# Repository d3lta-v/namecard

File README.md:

# Ziyue's Namecard

> An enhanced µCurrent Gold and tinyCurrent Derivative

Hi, Ziyue here! You probably received my namecard and you might be wondering what it is or how to use it. It is a fully functional professional low current measurement device, derived from the [µCurrent](https://www.eevblog.com/projects/ucurrent/) made by Dave Jones of EEVBLOG fame, and [tinyCurrent](https://github.com/nfhw/tinycurrent) by [n-fuse GmbH](https://www.n-fuse.co/contact.html). Handy for an EE engineer and a great addition to any EE lab. 

This version has several enhancements that makes it even better for measuring modern devices, especially if you work extensively with USB powered and embedded MCU / RF devices with fast current transients:

- **BNC Connector** to reduce pickup noise while measuring with an oscilloscope. You can use a short BNC female-female adapter to plug this device directly into your oscilloscope instead of relying on a banana jack to BNC cable
- **Higher Positive Dynamic Current Range** by soldering the JP1 jumper closed, up to 2.5A. This will disable sensing of negative currents, which will be clipped to 0V on the voltage output
- **Dedicated USB-C Ports** for current profiling a USB device directly, such as a microcontroller, RF module or other power constrained IoT devices
- **SMD Pads for optional C5, C6 capacitors** to add capacitors on virtual ground rails which prevents oscillation with capacitive loads

## Kit Contents

- PCB with all SMD components pre-soldered
- 2x DP3T switches
- 4x Banana jacks, 2 red and 2 black
- 1x CR2032 battery holder
- 1x BNC connector

Batteries not included, you will need to use your own CR2032 battery

Please solder the through hole components onto the board as per the instructions below.

> [!WARNING]
> The first revision of this board has a silkscreen defect. The battery holder must be soldered in the OPPOSITE direction as indicated by the silkscreen. Refer to the image in the steps below for the correct orientation

1. Solder the CR2032 battery holder
    - 
    - Alternatively, you can also solder wires directly to the battery terminals to attach an external power supply. Ensure your choice of external power is extremely linear with very low noise. Primary cells such as batteries are most suitable for this
2. Solder the BNC connector
    - 
3. Solder the two DP3T slide switches
    - 
4. Screw in the 4 banana jacks into all of the terminals, ensuring that the colors are matched to the positive/negative terminals
    - 
5. (Optional) Solder the JP1 jumper if you do not intend to measure any negative currents. Doing this will double the dynamic range of the device.

## Usage

1. Connect the device under test in loop **on the low side** so that the current flow is from **+** to **-**.
2. Connect a suitable voltage measurement device such as a digital multimeter or an oscilloscope (via BNC) on the output side via either the banana jacks or BNC connector.
3. Turn on the device and read the current on the voltage measurement device in the mV range as if it were mA/µA/nA.

A demo of using this device with an oscilloscope can be seen below:

https://github.com/user-attachments/assets/78531d4b-4d0c-471a-add1-b3f7db313485

## Specifications

### Absolute Maximum Ratings

| Parameter                        | Test Conditions | Min | Typ | Max | Unit |
| -------------------------------- | --------------- | --- | --- | --- | ---- |
| $I_{\text{max}}$ Maximum current |                 |     |     | 5   | A    |
| $V_{\text{cc}}$ Supply voltage   |                 |     |     | 5.5 | V    |

> [!WARNING]
> This device has NO input current protection to reduce burden voltage to a minimum. Do NOT overload the device.

### Electrical Characteristics

| Parameter                                             | Test Conditions             | Min   | Typ  | Max  | Unit   |
| ----------------------------------------------------- | --------------------------- | ----- | ---- | ---- | ------ |
| $I_{\text{nA}}$ Dynamic range of current in nA mode   | $V_{\text{cc}}=2.9\text{V}$ | -1250 |      | 1250 | nA     |
| $I_{\mu\text{A}}$ Dynamic range of current in µA mode | $V_{\text{cc}}=2.9\text{V}$ | -1250 |      | 1250 | µA     |
| $I_{\text{mA}}$ Dynamic range of current in mA mode   | $V_{\text{cc}}=2.9\text{V}$ | -1250 |      | 1250 | mA     |
| $V_{\text{cc}}$ Supply voltage                        |                             | 2.65  |      | 4.5    | V      |
| Resolution in nA mode                                 | On 3.5 digit DMM            |       | 1000 |      | pA     |
|                                                       | On 4.5 digit DMM            |       | 100  |      | pA     |
|                                                       | On 5.5 digit DMM            |       | 10   |      | pA     |
| Accuracy                                              | In µA and nA ranges         | -0.05 |      | 0.05 | %      |
|                                                       | In mA range                 | -0.1  |      | 0.1  | %      |
| $V_{\text{o,off}}$ Output Offset Voltage              |                             | -30   |      | 30   | µV     |
| Temperature Drift                                     | In µA and nA ranges         |       |      | 10   | ppm/˚C |
|                                                       | In mA range                 |       |      | 15   | ppm/˚C |
| Noise                                                 |                             |       |      | -90  | dBV    |
| THD                                                   |                             |       |      | -60  | dB     |
| Bandwidth (-3dB)                                      |                             |       | 300  |      | kHz    |

> Note that in nA mode, contact resistance will need to be accounted for, with an additional 10 µV bias on the output voltage due to the shunt resistor.

In ordinary operations in which virtual ground voltage $V_{\text{VGND}}=\frac{V_{\text{cc}}}{2}$, you can calculate the output voltage dynamic range using the formula:

$$
V_{\text{dynamic}} = \pm \left(\frac{V_{\text{cc}}}{2} - 200 \text{mV}\right)
$$

If you short the JP1 jumper, which sets the virtual ground voltage $V_{\text{VGND}}=0$, the new dynamic range will purely be in the positive range:

$$
V_{\text{dynamic}} = V_{\text{cc}} - 200 \text{mV}
$$

In general, this board has similar specifications to the [original µCurrent Gold](https://www.eevblog.com/projects/ucurrent/).

## Licenses

The circuit schematics of this project are made available under the
[CC-BY-SA](https://creativecommons.org/licenses/by-sa/3.0/) license.

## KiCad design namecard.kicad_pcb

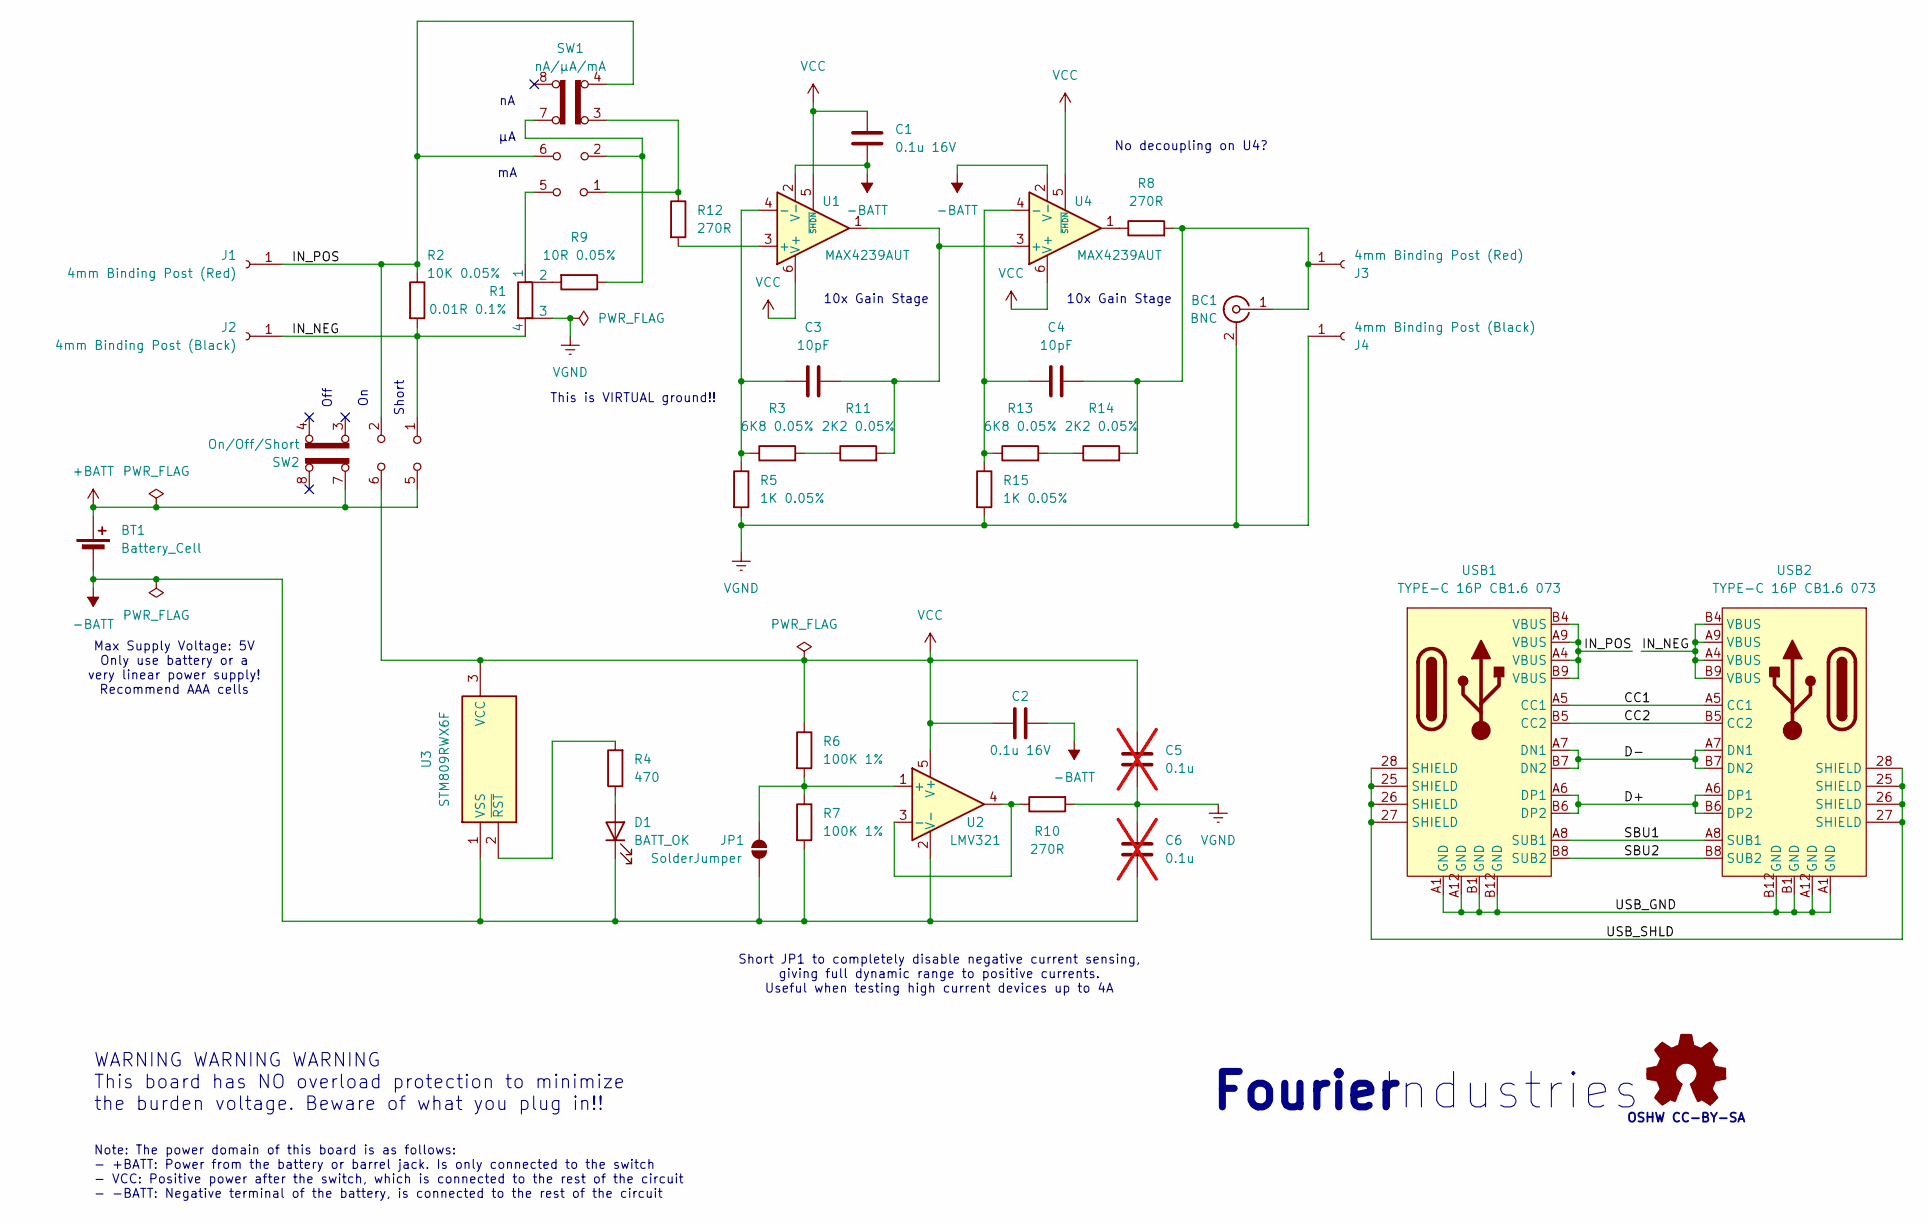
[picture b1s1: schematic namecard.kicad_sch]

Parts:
BC1: BNC; 0731000105
BT1: Battery_Cell; Battery_BAT-TH_BS-02-A1AJ010; JLCPCB C5239862
C1, C2: 0.1u 16V; C_0603_1608Metric
C3, C4: 10pF; C_0603_1608Metric
C5, C6: 0.1u; C_0805_2012Metric; not fitted
D1: BATT_OK; LED_0805_2012Metric; JLCPCB C2296
J1, J3: 4mm Binding Post (Red); Banana_Jack_1Pin_4mm
J2, J4: 4mm Binding Post (Black); Banana_Jack_1Pin_4mm
JP1: SolderJumper; SolderJumper-2_P1.3mm_Open_TrianglePad1.0x1.5mm
R1: 0.01R 0.1%; R_Shunt_Resi_PCSR2512_6332Metric
R2: 10K 0.05%; R_0603_1608Metric
R3, R13: 6K8 0.05%; R_0603_1608Metric
R4: 470; R_0603_1608Metric
R5, R15: 1K 0.05%; R_0603_1608Metric
R6, R7: 100K 1%; R_0603_1608Metric
R8, R10, R12: 270R; R_0603_1608Metric
R9: 10R 0.05%; R_0805_2012Metric
R11, R14: 2K2 0.05%; R_0603_1608Metric
SW1: nA/µA/mA; L203111MS02Q
SW2: On/Off/Short; L203111MS02Q
SYM1: Logo_Open_Hardware_Small; OSHW-Logo2_9.8x8mm_SilkScreen
U1, U4: MAX4239AUT; SOT-23-6
U2: LMV321; SOT-23-5; JLCPCB C7972
U3: STM809RWX6F; SOT103P237X112-3N; Manufacturer_Part_Number STM809RWX6F; Mouser Part Number 511-STM809RWX6F
USB1, USB2: TYPE-C 16P CB1.6 073; USB-C-SMD_SHOU_TYPE-C-16P-CB1.6; LCSC Part C2906290

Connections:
+BATT: BT1.1 (+), SW2.5 (B), SW2.7 (C)
-BATT: BT1.2 (-), C1.2, C2.2, C6.2, D1.1 (K), JP1.1 (A), R7.2, U1.2 (V-), U2.2 (V-), U3.1 (VSS), U4.2 (V-)
/CC1: USB1.A5 (CC1), USB2.A5 (CC1)
/CC2: USB1.B5 (CC2), USB2.B5 (CC2)
/D+: USB1.A6 (DP1), USB1.B6 (DP2), USB2.A6 (DP1), USB2.B6 (DP2)
/D-: USB1.A7 (DN1), USB1.B7 (DN2), USB2.A7 (DN1), USB2.B7 (DN2)
/IN_NEG: J2.1, R1.4, R2.2, SW2.1 (A), USB2.A4 (VBUS), USB2.A9 (VBUS), USB2.B4 (VBUS), USB2.B9 (VBUS)
/IN_POS: J1.1, R2.1, SW1.4 (A), SW1.6 (C), SW2.2 (B), USB1.A4 (VBUS), USB1.A9 (VBUS), USB1.B4 (VBUS), USB1.B9 (VBUS)
/SBU1: USB1.A8 (SUB1), USB2.A8 (SUB1)
/SBU2: USB1.B8 (SUB2), USB2.B8 (SUB2)
/USB_GND: USB1.A1 (GND), USB1.A12 (GND), USB1.B1 (GND), USB1.B12 (GND), USB2.A1 (GND), USB2.A12 (GND), USB2.B1 (GND), USB2.B12 (GND)
/USB_SHLD: USB1.25 (SHIELD), USB1.26 (SHIELD), USB1.27 (SHIELD), USB1.28 (SHIELD), USB2.25 (SHIELD), USB2.26 (SHIELD), USB2.27 (SHIELD), USB2.28 (SHIELD)
unnamed: BC1.1 (In), C4.2, J3.1, R8.2, R14.2
unnamed: D1.2 (A), R4.1
unnamed: JP1.2 (B), R6.2, R7.1, U2.1 (+)
unnamed: R1.1, SW1.5 (B)
unnamed: R1.2, R9.2
unnamed: R8.1, U4.1
unnamed: R9.1, SW1.2 (B), SW1.7 (C)
unnamed: R3.2, R11.1
unnamed: R12.1, SW1.1 (A), SW1.3 (C)
unnamed: R13.2, R14.1
unnamed: R12.2, U1.3 (+)
unnamed: C3.1, R3.1, R5.1, U1.4 (-)
unnamed: R10.1, U2.3 (-), U2.4
unnamed: R4.2, U3.2 (~RST)
unnamed: C3.2, R11.2, U1.1, U4.3 (+)
unnamed: C4.1, R13.1, R15.1, U4.4 (-)
VCC: C1.1, C2.1, C5.1, R6.1, SW2.6 (C), U1.5 (~SHDN), U1.6 (V+), U2.5 (V+), U3.3 (VCC), U4.5 (~SHDN), U4.6 (V+)
VGND: BC1.2 (Ext), C5.2, C6.1, J4.1, R1.3, R5.2, R10.2, R15.2

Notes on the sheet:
Fourier
Industries
10x Gain Stage
Off
This is VIRTUAL ground!!
WARNING WARNING WARNING This board has NO overload protection to minimize the burden voltage. Beware of what you plug in!!
Max Supply Voltage: 5V Only use battery or a very linear power supply! Recommend AAA cells
Short
Note: The power domain of this board is as follows: - +BATT: Power from the battery or barrel jack. Is only connected to the switch - VCC: Positive power after the switch, which is connected to the rest of the circuit - -BATT: Negative terminal of the battery, is connected to the rest of the circuit
OSHW CC-BY-SA
Short JP1 to completely disable negative current sensing, giving full dynamic range to positive currents. Useful when testing high current devices up to 4A
No decoupling on U4?

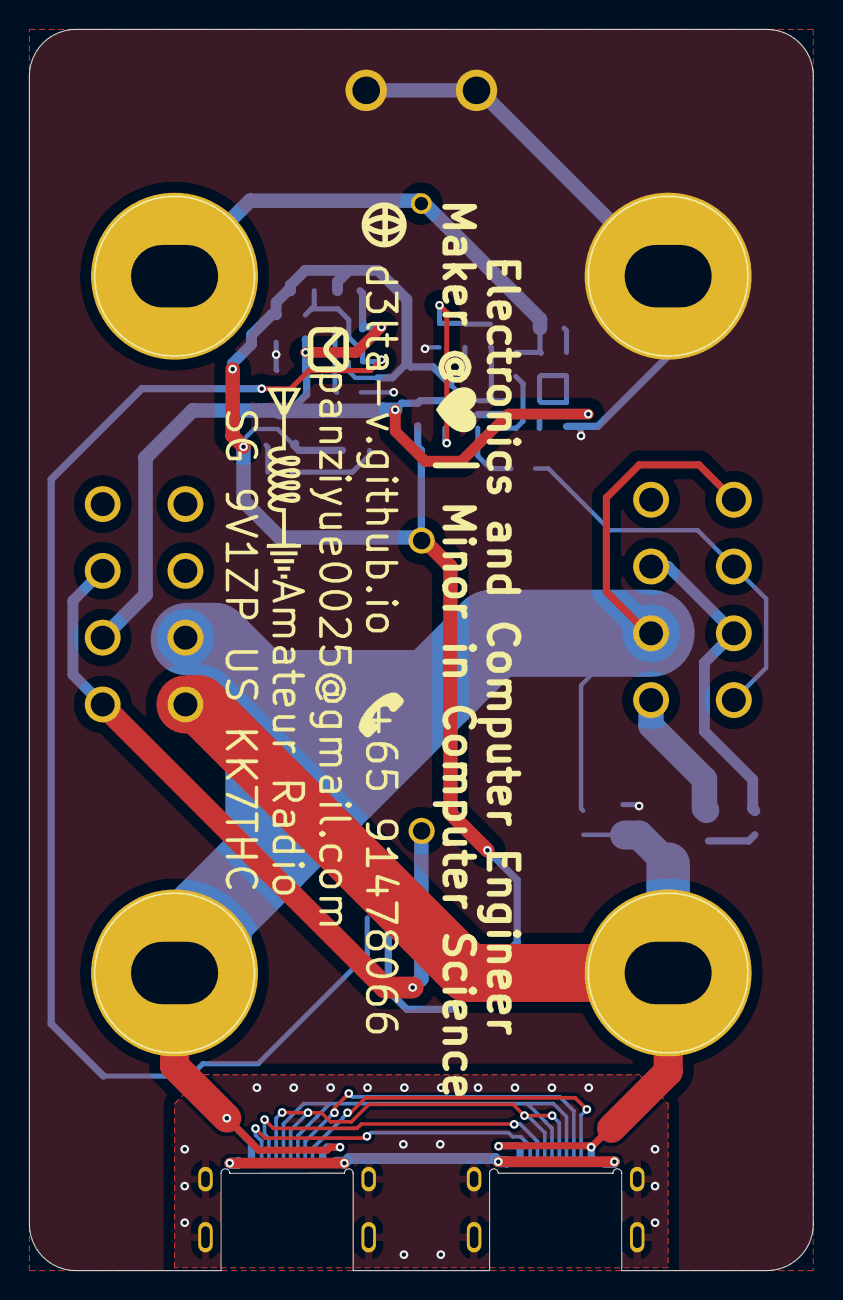
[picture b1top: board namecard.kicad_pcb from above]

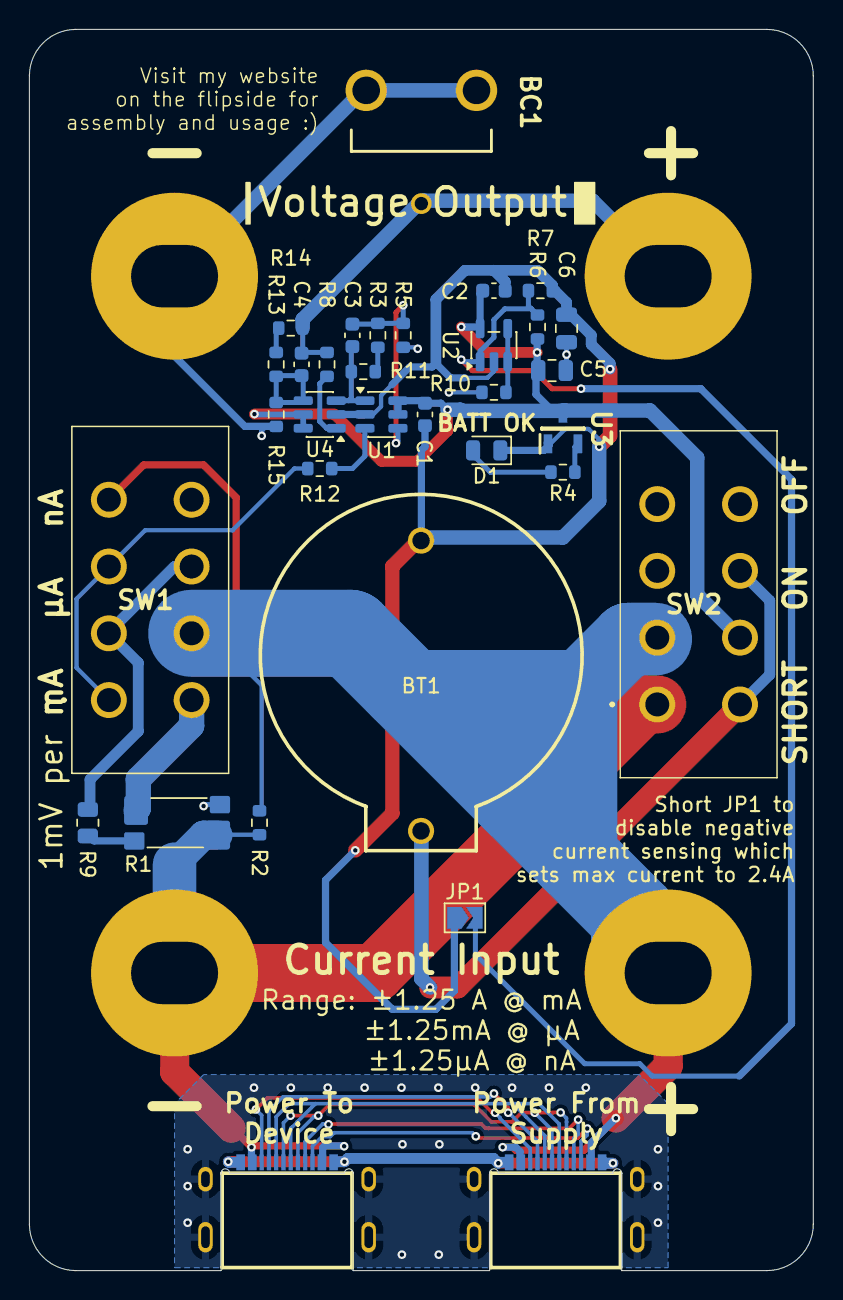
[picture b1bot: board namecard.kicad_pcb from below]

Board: 2 copper layers, 54.0 x 85.5 mm, 37 parts (33 on the bottom side), 30 nets.

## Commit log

2026-01-31 added video to README
